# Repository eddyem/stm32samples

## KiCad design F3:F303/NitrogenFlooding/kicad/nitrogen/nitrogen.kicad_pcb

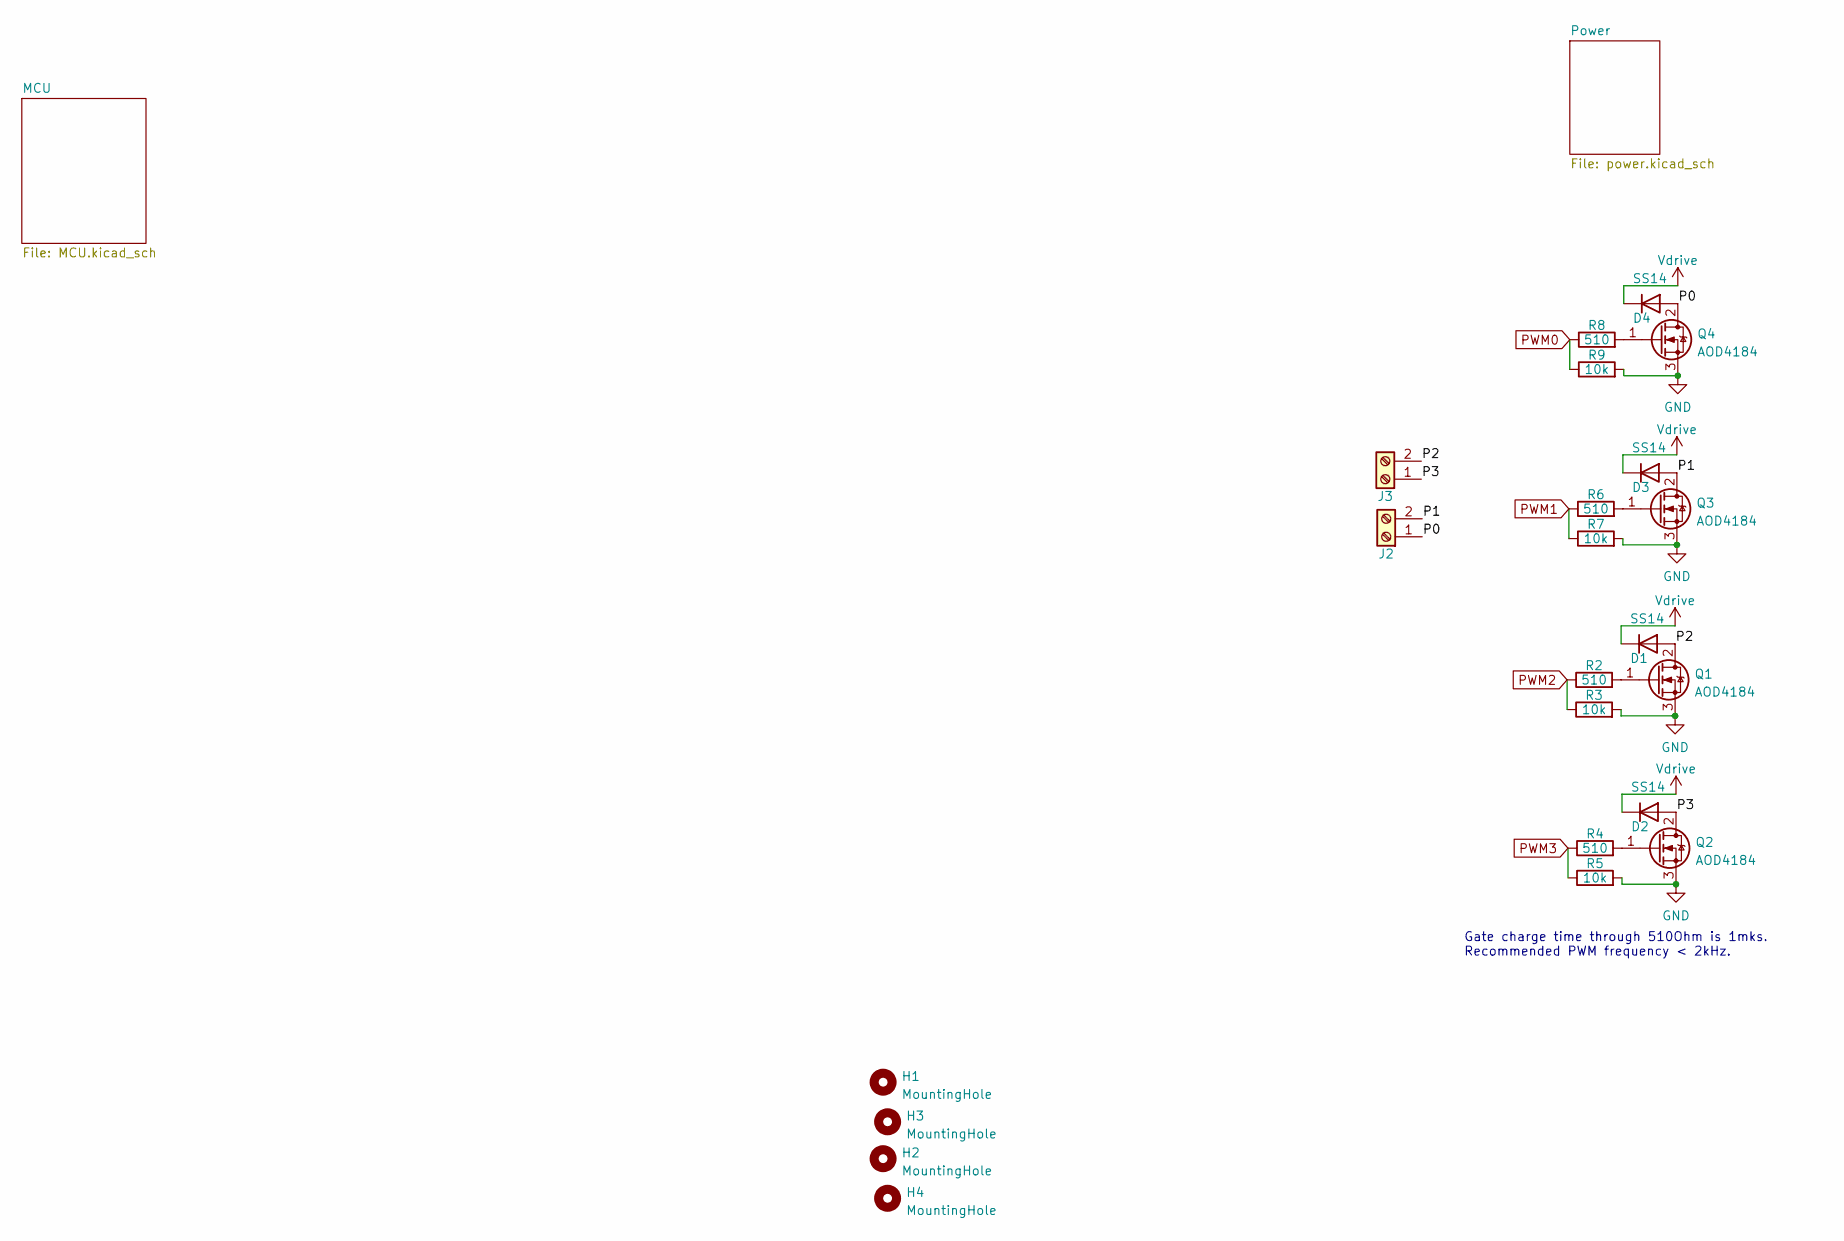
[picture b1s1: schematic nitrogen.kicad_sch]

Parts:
D1, D2, D3, D4: SS14; D_SMA_Handsoldering
H1, H2, H3, H4: MountingHole; MountingHole_3.2mm_M3_DIN965_Pad
J2, J3: Screw_Terminal_01x02; TerminalBlock_Phoenix_MKDS-1,5-2_1x02_P5.00mm_Horizontal
Q1, Q2, Q3, Q4: AOD4184; TO-252-2
R2, R4, R6, R8: 510; R_0603_1608Metric_Pad0.98x0.95mm_HandSolder
R3, R5, R7, R9: 10k; R_0603_1608Metric_Pad0.98x0.95mm_HandSolder

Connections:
/P0: D4.2 (A), J2.1, Q4.2 (D)
/P1: D3.2 (A), J2.2, Q3.2 (D)
/P2: D1.2 (A), J3.2, Q1.2 (D)
/P3: D2.2 (A), J3.1, Q2.2 (D)
GND: Q1.3 (S), Q2.3 (S), Q3.3 (S), Q4.3 (S), R3.2, R5.2, R7.2, R9.2; also elsewhere on the board
unnamed: Q1.1 (G), R2.2
unnamed: Q2.1 (G), R4.2
unnamed: Q3.1 (G), R6.2
unnamed: Q4.1 (G), R8.2
PWM0: R8.1, R9.1; also elsewhere on the board
PWM1: R6.1, R7.1; also elsewhere on the board
PWM2: R2.1, R3.1; also elsewhere on the board
PWM3: R4.1, R5.1; also elsewhere on the board
Vdrive: D1.1 (K), D2.1 (K), D3.1 (K), D4.1 (K); also elsewhere on the board

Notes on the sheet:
Gate charge time through 510Ohm is 1mks. Recommended PWM frequency < 2kHz.

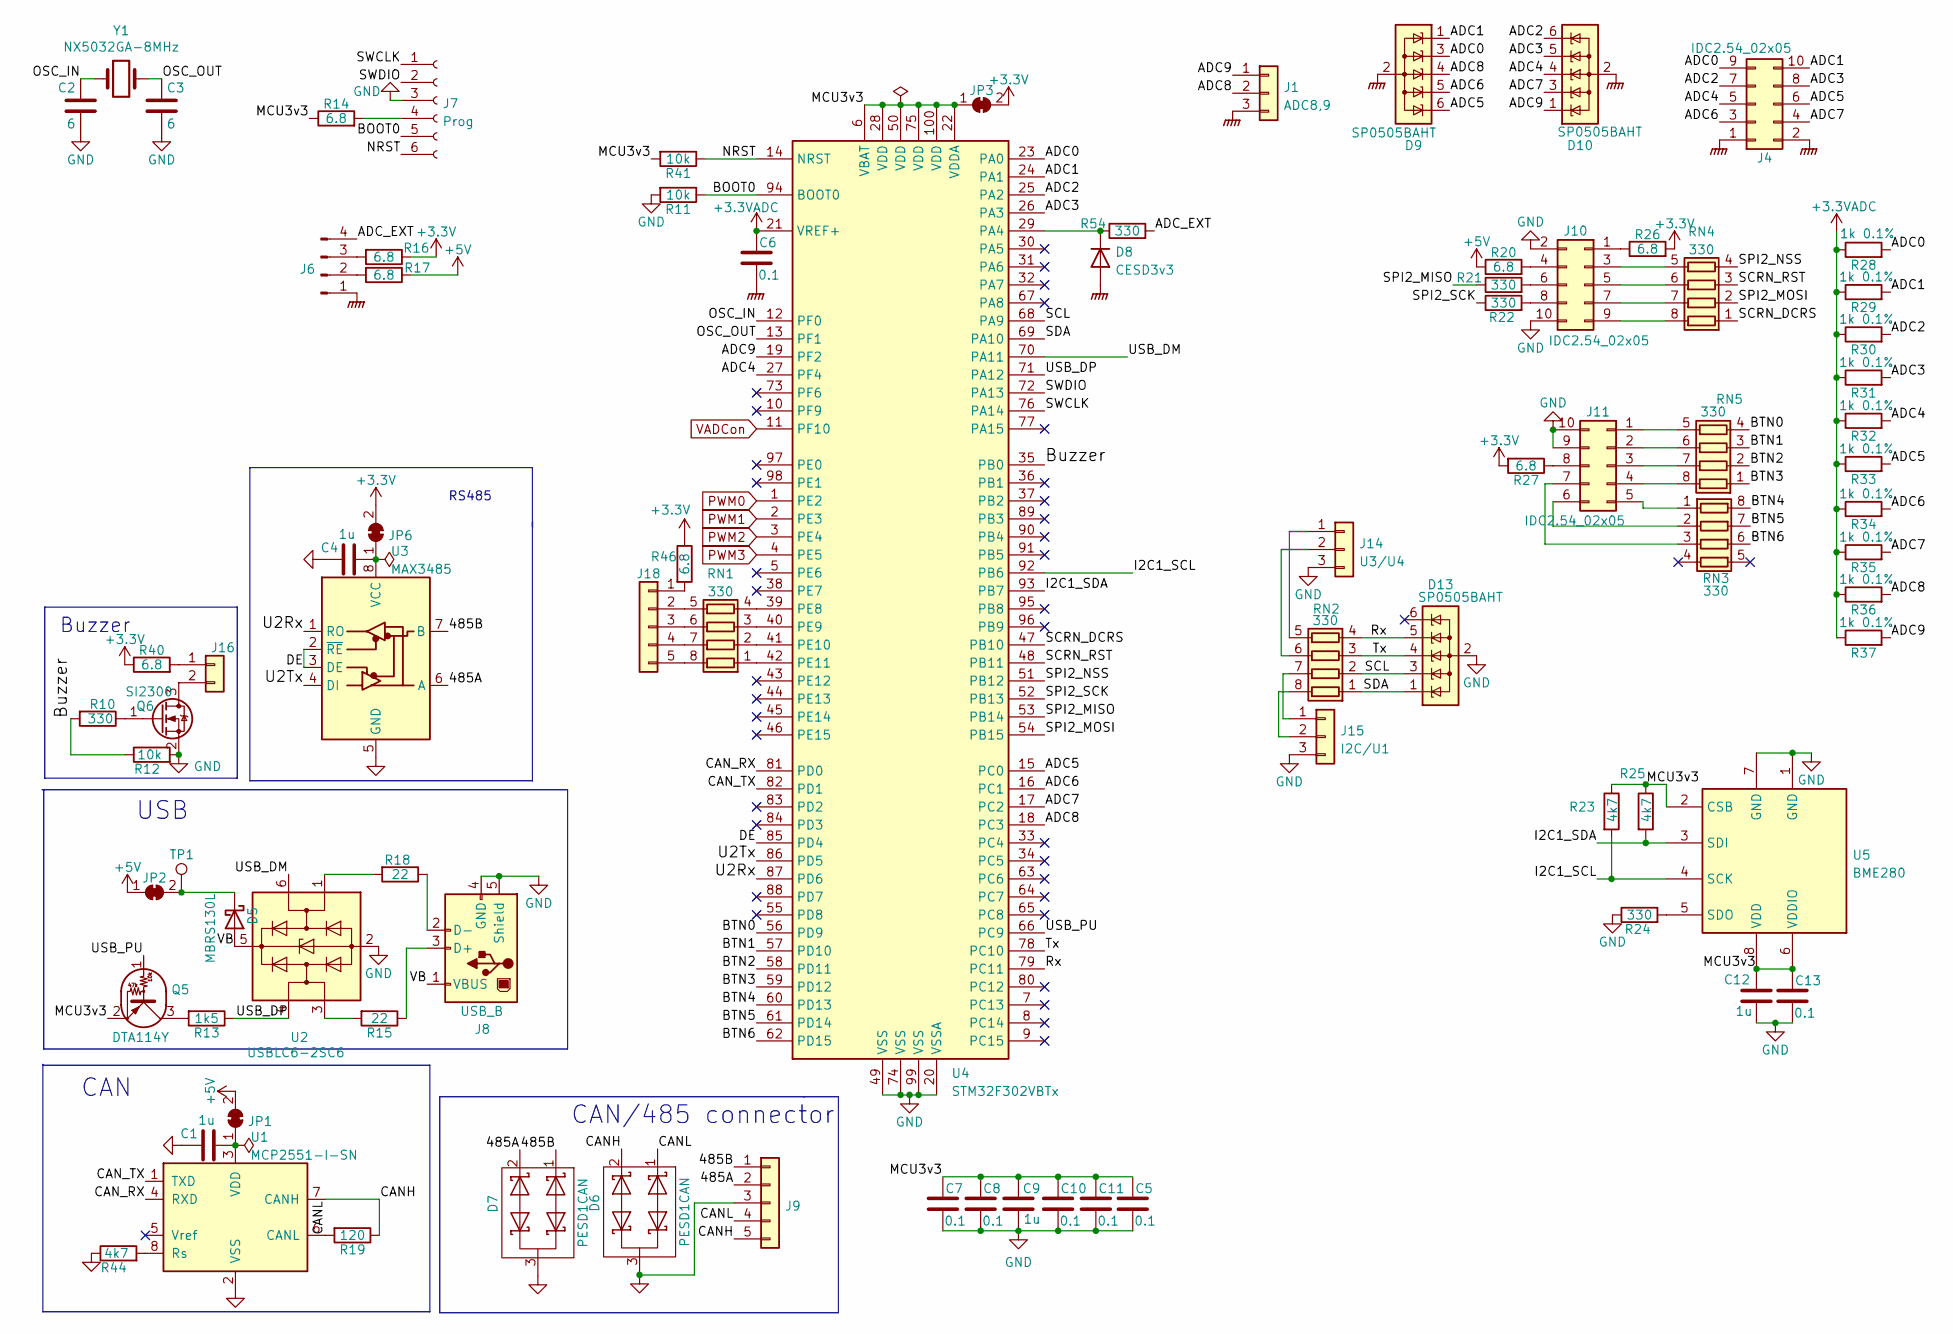
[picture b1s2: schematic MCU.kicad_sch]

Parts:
C1, C4, C9, C12: 1u; C_0603_1608Metric_Pad1.08x0.95mm_HandSolder
C2, C3: 6; C_0603_1608Metric_Pad1.08x0.95mm_HandSolder
C5, C6, C7, C8, C10, C11, C13: 0.1; C_0603_1608Metric_Pad1.08x0.95mm_HandSolder
D5: MBRS130L; D_SMB_Handsoldering
D6, D7: PESD1CAN; SOT-23
D8: CESD3v3; D_SOD-523
D9, D10, D13: SP0505BAHT; SOT-23-6
J1: ADC8,9; JST_EH_B3B-EH-A_1x03_P2.50mm_Vertical
J4, J10, J11: IDC2.54_02x05; IDC-Header_2x05_P2.54mm_Vertical
J6: ADCext; JST_EH_B4B-EH-A_1x04_P2.50mm_Vertical
J7: Prog; PinSocket_1x06_P1.27mm_Vertical
J8: USB_B; USB_B_TE_5787834_Vertical
J9: 485/CAN; JST_EH_B5B-EH-A_1x05_P2.50mm_Vertical
J14: U3/U4; JST_EH_B3B-EH-A_1x03_P2.50mm_Vertical
J15: I2C/U1; JST_EH_B3B-EH-A_1x03_P2.50mm_Vertical
J16: buzzer; PinSocket_1x02_P2.54mm_Vertical
J18: LEDs; JST_EH_B5B-EH-A_1x05_P2.50mm_Vertical
JP1: CAN; SolderJumper-2_P1.3mm_Open_TrianglePad1.0x1.5mm
JP2: USB5V; SolderJumper-2_P1.3mm_Open_TrianglePad1.0x1.5mm
JP3: MCU; SolderJumper-2_P1.3mm_Open_TrianglePad1.0x1.5mm
JP6: RS-485; SolderJumper-2_P1.3mm_Open_TrianglePad1.0x1.5mm
Q5: DTA114Y; SOT-323_SC-70_Handsoldering
Q6: SI2300; SOT-23_Handsoldering
R10, R21, R22, R24, R54: 330; R_0603_1608Metric_Pad0.98x0.95mm_HandSolder
R11, R12, R41: 10k; R_0603_1608Metric_Pad0.98x0.95mm_HandSolder
R13: 1k5; R_0603_1608Metric_Pad0.98x0.95mm_HandSolder
R14, R16, R17, R20, R26, R27, R40, R46: 6.8; R_0603_1608Metric_Pad0.98x0.95mm_HandSolder
R15, R18: 22; R_0603_1608Metric_Pad0.98x0.95mm_HandSolder
R19: 120; R_1210_3225Metric_Pad1.30x2.65mm_HandSolder
R23, R25, R44: 4k7; R_0603_1608Metric_Pad0.98x0.95mm_HandSolder
R28, R29, R30, R31, R32, R33, R34, R35, R36, R37: 1k 0.1%; R_0805_2012Metric_Pad1.20x1.40mm_HandSolder
RN1, RN2, RN3, RN4, RN5: 330; R_Array_Convex_4x0603
TP1: 5Vusb; TestPoint_THTPad_1.5x1.5mm_Drill0.7mm
U1: MCP2551-I-SN; SOIC-8_3.9x4.9mm_P1.27mm
U2: USBLC6-2SC6; SOT-23-6
U3: MAX3485; SO-8_3.9x4.9mm_P1.27mm
U4: STM32F302VBTx; LQFP-100_14x14mm_P0.5mm
U5: BME280; Bosch_LGA-8_2.5x2.5mm_P0.65mm_ClockwisePinNumbering
Y1: NX5032GA-8MHz; Crystal_SMD_5032-2Pin_5.0x3.2mm

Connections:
+3.3V: JP3.2 (B), JP6.2 (B), R16.1, R26.2, R27.2, R40.1, R46.1; also elsewhere on the board
+3.3VADC: C6.1, R28.1, R29.1, R30.1, R31.1, R32.1, R33.1, R34.1, R35.1, R36.1, R37.1, U4.21 (VREF+); also elsewhere on the board
+5V: JP1.2 (B), JP2.1 (A), R17.1, R20.1; also elsewhere on the board
/MCU/485A: D7.2 (K), J9.2, U3.6 (A)
/MCU/485B: D7.1 (K), J9.1, U3.7 (B)
/MCU/ADC0: D9.3 (K), J4.9, R28.2, U4.23 (PA0)
/MCU/ADC1: D9.1 (K), J4.10, R29.2, U4.24 (PA1)
/MCU/ADC2: D10.6 (K), J4.7, R30.2, U4.25 (PA2)
/MCU/ADC3: D10.5 (K), J4.8, R31.2, U4.26 (PA3)
/MCU/ADC4: D10.4 (K), J4.5, R32.2, U4.27 (PF4)
/MCU/ADC5: D9.6 (K), J4.6, R33.2, U4.15 (PC0)
/MCU/ADC6: D9.5 (K), J4.3, R34.2, U4.16 (PC1)
/MCU/ADC7: D10.3 (K), J4.4, R35.2, U4.17 (PC2)
/MCU/ADC8: D9.4 (K), J1.2, R36.2, U4.18 (PC3)
/MCU/ADC9: D10.1 (K), J1.1, R37.2, U4.19 (PF2)
/MCU/ADC_EXT: J6.4, R54.2
/MCU/BOOT0: J7.5, R11.1, U4.94 (BOOT0)
/MCU/BTN0: RN5.4 (R4.1), U4.56 (PD9)
/MCU/BTN1: RN5.3 (R3.1), U4.57 (PD10)
/MCU/BTN2: RN5.2 (R2.1), U4.58 (PD11)
/MCU/BTN3: RN5.1 (R1.1), U4.59 (PD12)
/MCU/BTN4: RN3.8 (R1.2), U4.60 (PD13)
/MCU/BTN5: RN3.7 (R2.2), U4.61 (PD14)
/MCU/BTN6: RN3.6 (R3.2), U4.62 (PD15)
/MCU/Buzzer: R10.2, R12.1, U4.35 (PB0)
/MCU/CANH: D6.2 (K), J9.5, R19.1, U1.7 (CANH)
/MCU/CANL: D6.1 (K), J9.4, R19.2, U1.6 (CANL)
/MCU/CAN_RX: U1.4 (RXD), U4.81 (PD0)
/MCU/CAN_TX: U1.1 (TXD), U4.82 (PD1)
/MCU/DE: U3.2 (~RE), U3.3 (DE), U4.85 (PD4)
/MCU/I2C1_SCL: R23.2, U4.92 (PB6), U5.4 (SCK)
/MCU/I2C1_SDA: R25.2, U4.93 (PB7), U5.3 (SDI)
/MCU/MCU3v3: C5.1, C7.1, C8.1, C9.1, C10.1, C11.1, C12.1, C13.1, JP3.1 (A), Q5.2 (E), R14.1, R23.1, R25.1, R41.2, U4.6 (VBAT), U4.22 (VDDA), U4.28 (VDD), U4.50 (VDD), U4.75 (VDD), U4.100 (VDD), U5.2 (CSB), U5.6 (VDDIO), U5.8 (VDD)
/MCU/NRST: J7.6, R41.1, U4.14 (NRST)
/MCU/OSC_IN: C2.1, U4.12 (PF0), Y1.1
/MCU/OSC_OUT: C3.1, U4.13 (PF1), Y1.2
/MCU/Rx: D13.5 (K), RN2.4 (R4.1), U4.79 (PC11)
/MCU/SCL: D13.3 (K), RN2.2 (R2.1), U4.68 (PA9)
/MCU/SCRN_DCRS: RN4.1 (R1.1), U4.47 (PB10)
/MCU/SCRN_RST: RN4.3 (R3.1), U4.48 (PB11)
/MCU/SDA: D13.1 (K), RN2.1 (R1.1), U4.69 (PA10)
/MCU/SPI2_MISO: R21.1, U4.53 (PB14)
/MCU/SPI2_MOSI: RN4.2 (R2.1), U4.54 (PB15)
/MCU/SPI2_NSS: RN4.4 (R4.1), U4.51 (PB12)
/MCU/SPI2_SCK: R22.1, U4.52 (PB13)
/MCU/SWCLK: J7.1, U4.76 (PA14)
/MCU/SWDIO: J7.2, U4.72 (PA13)
/MCU/Tx: D13.4 (K), RN2.3 (R3.1), U4.78 (PC10)
/MCU/U2Rx: U3.1 (RO), U4.87 (PD6)
/MCU/U2Tx: U3.4 (DI), U4.86 (PD5)
/MCU/USB_DM: U2.6 (I/O1), U4.70 (PA11)
/MCU/USB_DP: R13.1, U2.4 (I/O2), U4.71 (PA12)
/MCU/USB_PU: Q5.1 (B), U4.66 (PC9)
/MCU/VB: D5.2 (A), J8.1 (VBUS), U2.5 (VBUS)
GND: C1.1, C2.2, C3.2, C4.1, C5.2, C7.2, C8.2, C9.2, C10.2, C11.2, C12.2, C13.2, D6.3 (O), D7.3 (O), D13.2 (A), J7.3, J8.4 (GND), J8.5 (Shield), J9.3, J10.2, J10.10, J11.9, J11.10, J14.3, J15.3, Q6.2 (S), R11.2, R12.2, R24.1, R44.1, U1.2 (VSS), U2.2 (GND), U3.5 (GND), U4.20 (VSSA), U4.49 (VSS), U4.74 (VSS), U4.99 (VSS), U5.1 (GND), U5.7 (GND); also elsewhere on the board
GNDPWR: C6.2, D8.2 (A), D9.2 (A), D10.2 (A), J1.3, J4.1, J4.2, J6.1; also elsewhere on the board
unnamed: C1.2, JP1.1 (A), U1.3 (VDD)
unnamed: C4.2, JP6.1 (A), U3.8 (VCC)
unnamed: D5.1 (K), JP2.2 (B), TP1.1
unnamed: D8.1 (K), R54.1, U4.29 (PA4)
unnamed: J6.2, R17.2
unnamed: J6.3, R16.2
unnamed: J7.4, R14.2
unnamed: J8.2 (D-), R18.1
unnamed: J8.3 (D+), R15.1
unnamed: J10.1, R26.1
unnamed: J10.3, RN4.5 (R4.2)
unnamed: J10.4, R20.2
unnamed: J10.5, RN4.6 (R3.2)
unnamed: J10.6, R21.2
unnamed: J10.7, RN4.7 (R2.2)
unnamed: J10.8, R22.2
unnamed: J10.9, RN4.8 (R1.2)
unnamed: J11.1, RN5.5 (R4.2)
unnamed: J11.2, RN5.6 (R3.2)
unnamed: J11.3, RN5.7 (R2.2)
unnamed: J11.4, RN5.8 (R1.2)
unnamed: J11.5, RN3.1 (R1.1)
unnamed: J11.6, RN3.2 (R2.1)
unnamed: J11.7, RN3.3 (R3.1)
unnamed: J11.8, R27.1
unnamed: J14.1, RN2.5 (R4.2)
unnamed: J14.2, RN2.6 (R3.2)
unnamed: J15.1, RN2.7 (R2.2)
unnamed: J15.2, RN2.8 (R1.2)
unnamed: J16.1, R40.2
unnamed: J16.2, Q6.3 (D)
unnamed: J18.1, R46.2
unnamed: J18.2, RN1.5 (R4.2)
unnamed: J18.3, RN1.6 (R3.2)
unnamed: J18.4, RN1.7 (R2.2)
unnamed: J18.5, RN1.8 (R1.2)
unnamed: Q5.3 (C), R13.2
unnamed: Q6.1 (G), R10.1
unnamed: R15.2, U2.3 (I/O2)
unnamed: R18.2, U2.1 (I/O1)
unnamed: R24.2, U5.5 (SDO)
unnamed: R44.2, U1.8 (Rs)
unnamed: RN1.1 (R1.1), U4.42 (PE11)
unnamed: RN1.2 (R2.1), U4.41 (PE10)
unnamed: RN1.3 (R3.1), U4.40 (PE9)
unnamed: RN1.4 (R4.1), U4.39 (PE8)
PWM0: U4.1 (PE2); also elsewhere on the board
PWM1: U4.2 (PE3); also elsewhere on the board
PWM2: U4.3 (PE4); also elsewhere on the board
PWM3: U4.4 (PE5); also elsewhere on the board
VADCon: U4.11 (PF10); also elsewhere on the board

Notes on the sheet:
USB
RS485
Buzzer
CAN/485 connector
CAN

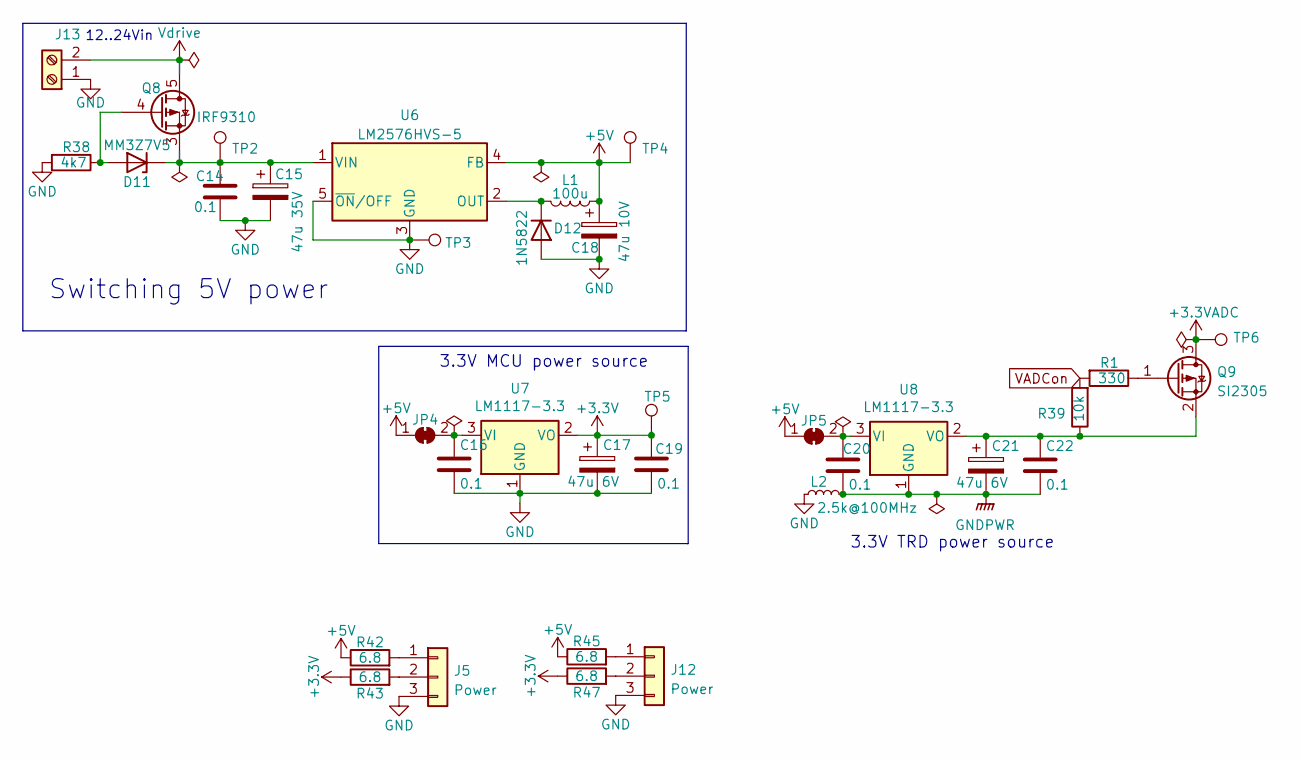
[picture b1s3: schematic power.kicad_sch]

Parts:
C14, C16, C19, C20, C22: 0.1; C_0603_1608Metric_Pad1.08x0.95mm_HandSolder
C15: 47u 35V; CP_EIA-6032-28_Kemet-C_Pad2.25x2.35mm_HandSolder
C17, C21: 47u 6V; CP_EIA-3216-18_Kemet-A_Pad1.58x1.35mm_HandSolder
C18: 47u 10V; CP_EIA-6032-28_Kemet-C_Pad2.25x2.35mm_HandSolder
D11: MM3Z7V5; D_0805_2012Metric_Pad1.15x1.40mm_HandSolder
D12: 1N5822; D_DO-201_P3.81mm_Vertical_AnodeUp
J5, J12: Power; JST_EH_B3B-EH-A_1x03_P2.50mm_Vertical
J13: Screw_Terminal_01x02; TerminalBlock_Phoenix_MKDS-1,5-2_1x02_P5.00mm_Horizontal
JP4: 3v3; SolderJumper-2_P1.3mm_Open_TrianglePad1.0x1.5mm
JP5: Vadc; SolderJumper-2_P1.3mm_Open_TrianglePad1.0x1.5mm
L1: 100u; L_Toroid_Horizontal_D6.5mm_P10.00mm_Diameter7-5mm_Amidon-T25
L2: 2.5k@100MHz; L_0805_2012Metric_Pad1.15x1.40mm_HandSolder
Q8: IRF9310; SO-8_3.9x4.9mm_P1.27mm
Q9: SI2305; SOT-23_Handsoldering
R1: 330; R_0603_1608Metric_Pad0.98x0.95mm_HandSolder
R38: 4k7; R_0603_1608Metric_Pad0.98x0.95mm_HandSolder
R39: 10k; R_0603_1608Metric_Pad0.98x0.95mm_HandSolder
R42, R43, R45, R47: 6.8; R_0603_1608Metric_Pad0.98x0.95mm_HandSolder
TP2: Vin; TestPoint_THTPad_1.5x1.5mm_Drill0.7mm
TP3: Gnd; TestPoint_THTPad_1.5x1.5mm_Drill0.7mm
TP4: 5V; TestPoint_THTPad_1.5x1.5mm_Drill0.7mm
TP5: 3.3V; TestPoint_THTPad_1.5x1.5mm_Drill0.7mm
TP6: Vadc; TestPoint_THTPad_1.5x1.5mm_Drill0.7mm
U6: LM2576HVS-5; TO-263-5_TabPin3
U7, U8: LM1117-3.3; SOT-223-3_TabPin2

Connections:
+3.3V: C17.1, C19.1, R43.1, R47.1, TP5.1, U7.2 (VO); also elsewhere on the board
+3.3VADC: Q9.3 (D), TP6.1; also elsewhere on the board
+5V: C18.1, JP4.1 (A), JP5.1 (A), L1.1, R42.1, R45.1, TP4.1, U6.4 (FB); also elsewhere on the board
GND: C14.2, C15.2, C16.2, C17.2, C18.2, C19.2, D12.2 (A), J5.3, J12.3, J13.1, L2.1, R38.2, TP3.1, U6.3 (GND), U6.5 (~ON/OFF), U7.1 (GND); also elsewhere on the board
GNDPWR: C20.2, C21.2, C22.2, L2.2, U8.1 (GND); also elsewhere on the board
unnamed: C14.1, C15.1, D11.1 (K), Q8.1 (S), Q8.2 (S), Q8.3 (S), TP2.1, U6.1 (VIN)
unnamed: C16.1, JP4.2 (B), U7.3 (VI)
unnamed: C20.1, JP5.2 (B), U8.3 (VI)
unnamed: C21.1, C22.1, Q9.2 (S), R39.1, U8.2 (VO)
unnamed: D11.2 (A), Q8.4 (G), R38.1
unnamed: D12.1 (K), L1.2, U6.2 (OUT)
unnamed: J5.1, R42.2
unnamed: J5.2, R43.2
unnamed: J12.1, R45.2
unnamed: J12.2, R47.2
unnamed: Q9.1 (G), R1.1
VADCon: R1.2, R39.2; also elsewhere on the board
Vdrive: J13.2, Q8.5 (D), Q8.6 (D), Q8.7 (D), Q8.8 (D); also elsewhere on the board

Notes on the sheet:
Switching 5V power
3.3V MCU power source
12..24Vin
3.3V TRD power source

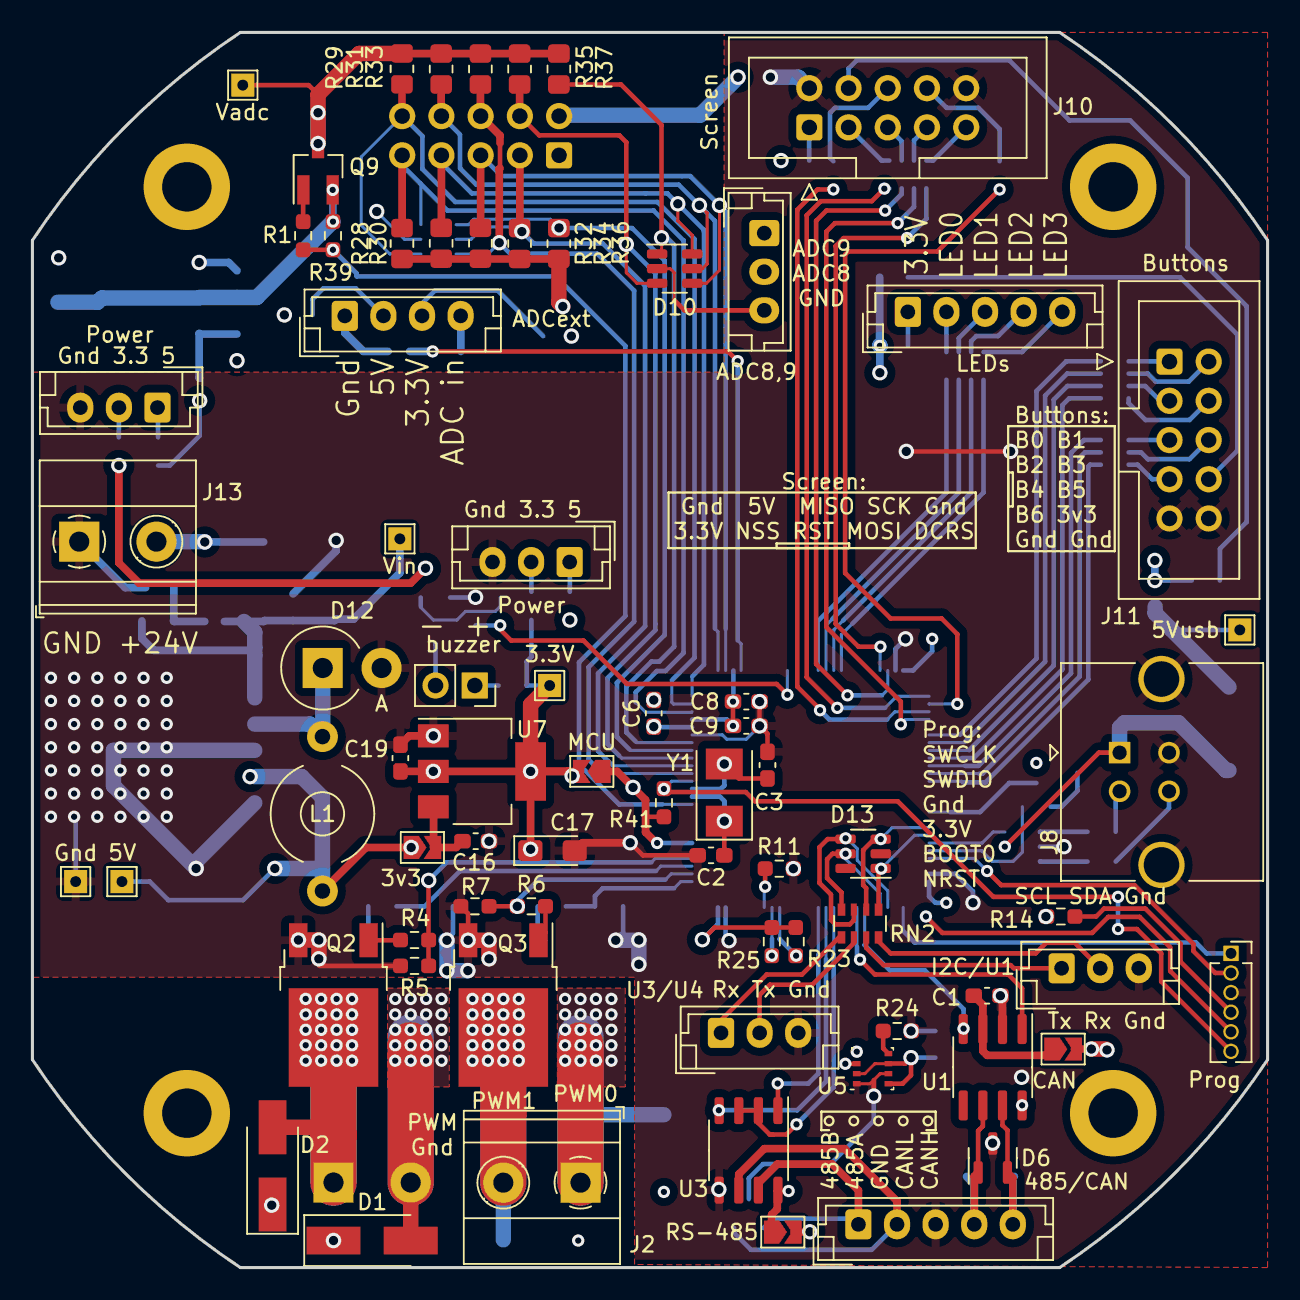
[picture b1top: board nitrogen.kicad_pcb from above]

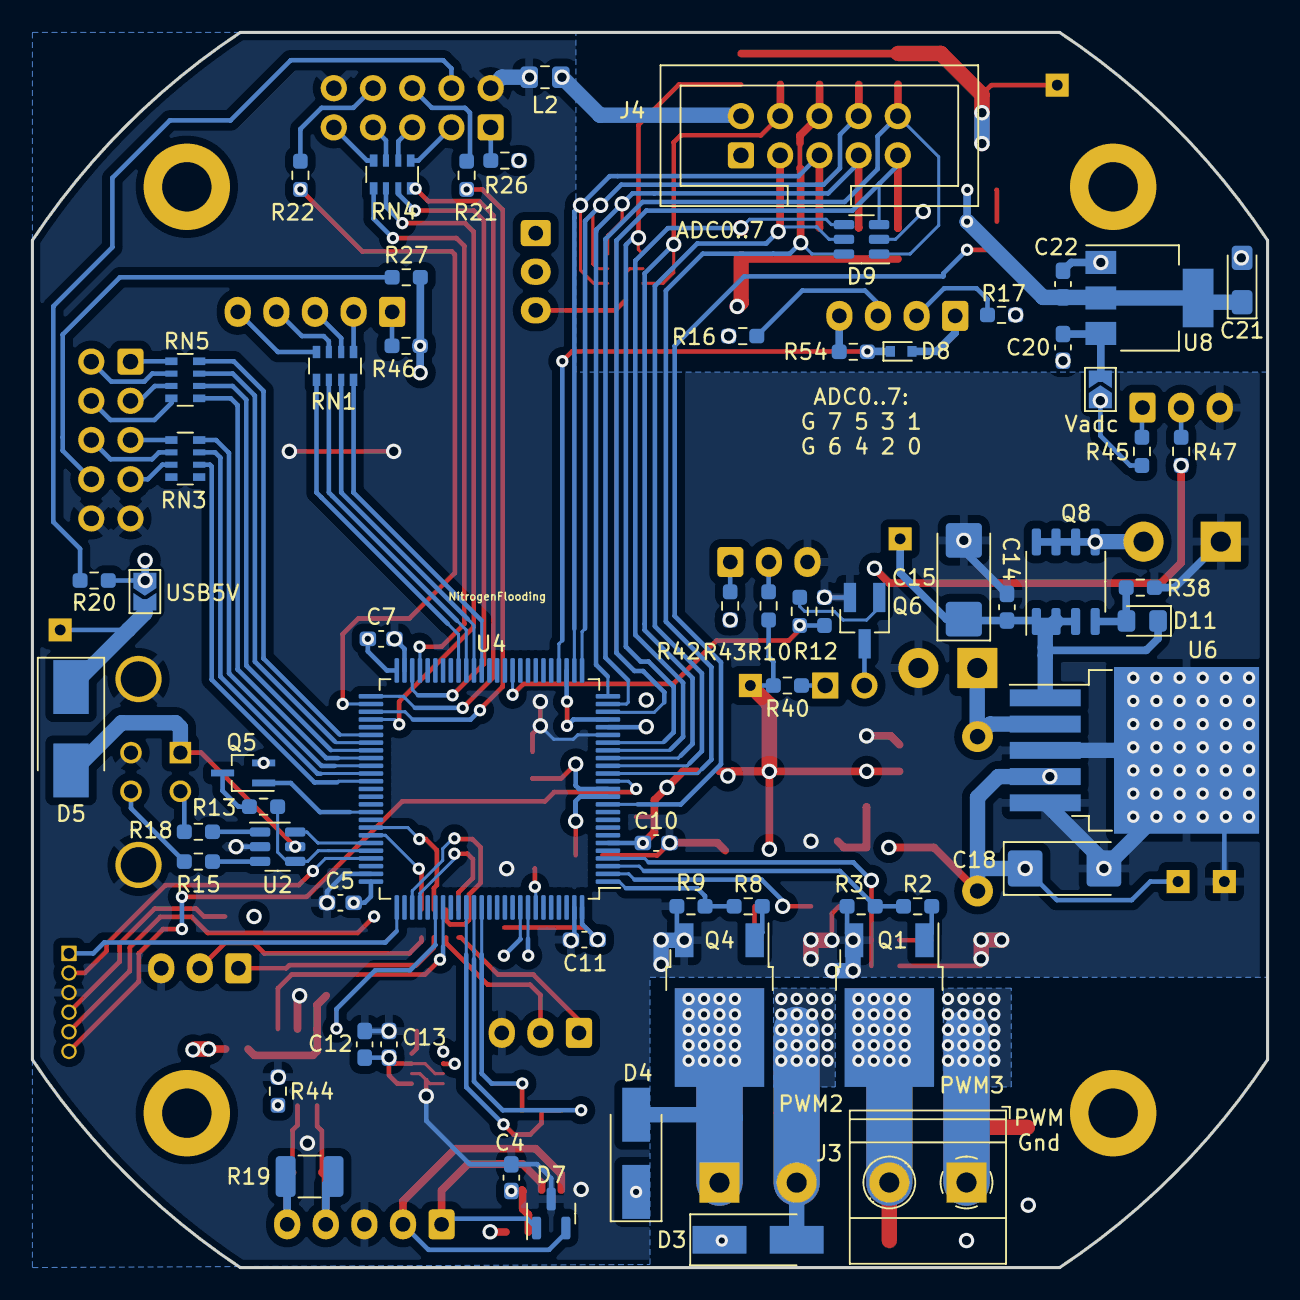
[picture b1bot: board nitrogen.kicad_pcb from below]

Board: 4 copper layers, 80.0 x 80.0 mm, 140 parts (64 on the bottom side), 127 nets.

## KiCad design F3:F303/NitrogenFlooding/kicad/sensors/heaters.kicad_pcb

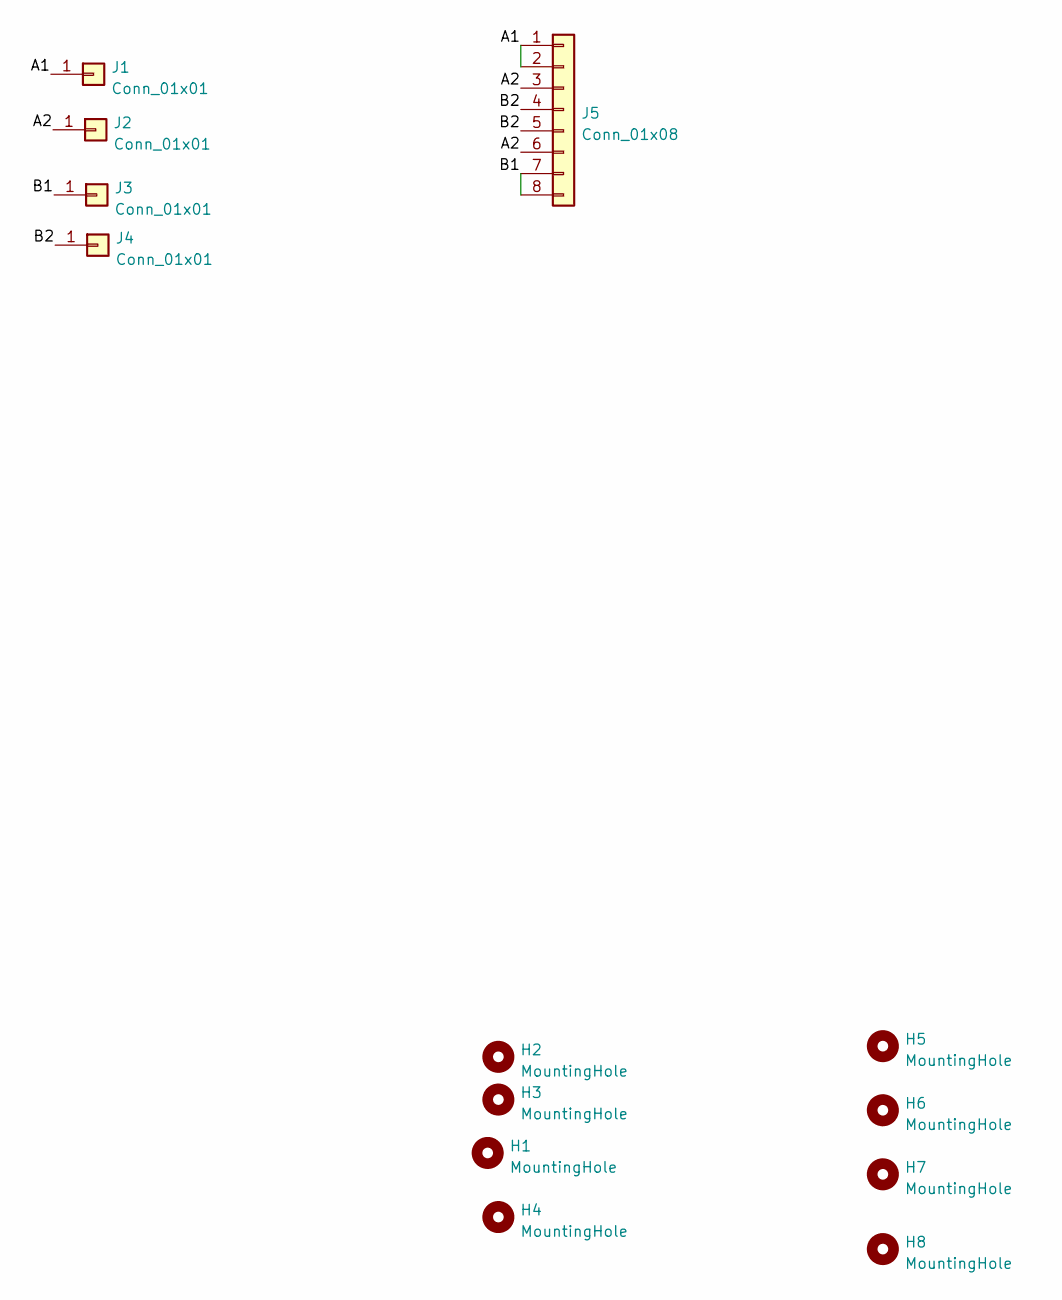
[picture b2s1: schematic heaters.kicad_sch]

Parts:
H1, H2, H3, H4: MountingHole; MountingHole_2mm
H5, H6, H7, H8: MountingHole; MountingHole_3.2mm_M3
J1, J2, J3, J4: Conn_01x01; PinSocket_1x01_P2.54mm_Vertical
J5: Conn_01x08; avia8

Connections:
/A1: J1.1, J5.1, J5.2
/A2: J2.1, J5.3, J5.6
/B1: J3.1, J5.7, J5.8
/B2: J4.1, J5.4, J5.5

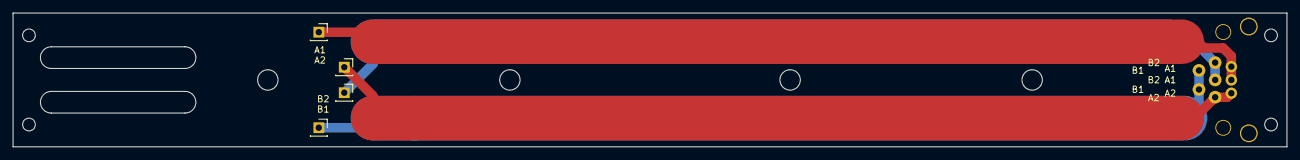
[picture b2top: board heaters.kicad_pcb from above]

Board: 2 copper layers, 200.0 x 21.0 mm, 13 parts (0 on the bottom side), 4 nets.

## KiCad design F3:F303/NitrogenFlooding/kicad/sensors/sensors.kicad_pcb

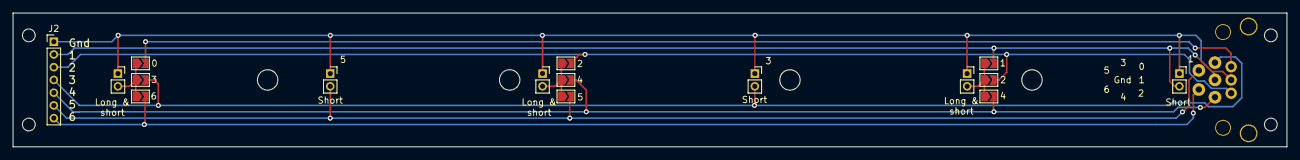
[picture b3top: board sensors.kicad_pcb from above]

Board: 2 copper layers, 200.0 x 21.0 mm, 25 parts (0 on the bottom side), 11 nets.

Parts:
H1, H2, H3, H4: MountingHole; MountingHole_2mm
H5, H6, H7, H8: MountingHole; MountingHole_3.2mm_M3
J1: Conn_01x08; avia8
J2: Conn_01x08; PinHeader_1x07_P2.00mm_Vertical
JP1: 1; SolderJumper-2_P1.3mm_Open_TrianglePad1.0x1.5mm
JP2, JP4: 2; SolderJumper-2_P1.3mm_Open_TrianglePad1.0x1.5mm
JP3, JP5: 4; SolderJumper-2_P1.3mm_Open_TrianglePad1.0x1.5mm
JP6: 5; SolderJumper-2_P1.3mm_Open_TrianglePad1.0x1.5mm
JP7: 0; SolderJumper-2_P1.3mm_Open_TrianglePad1.0x1.5mm
JP8: 3; SolderJumper-2_P1.3mm_Open_TrianglePad1.0x1.5mm
JP9: 6; SolderJumper-2_P1.3mm_Open_TrianglePad1.0x1.5mm
TH1, TH2, TH3, TH4, TH5, TH6: PT1000; PinSocket_1x02_P2.00mm_Vertical

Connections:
/S1: JP1.1 (A), JP2.1 (A), JP3.1 (A), TH2.2
/S3: JP4.1 (A), JP5.1 (A), JP6.1 (A), TH4.2
/S5: JP7.1 (A), JP8.1 (A), JP9.1 (A), TH6.2
/Sa0: J1.1, JP7.2 (B)
/Sa1: J1.2, J2.2, JP1.2 (B), TH1.2
/Sa2: J1.3, J2.3, JP2.2 (B), JP4.2 (B)
/Sa3: J1.4, J2.4, JP8.2 (B), TH3.2
/Sa4: J1.6, J2.5, JP3.2 (B), JP5.2 (B)
/Sa5: J1.7, J2.6, JP6.2 (B), TH5.2
/Sa6: J1.8, J2.7, JP9.2 (B)
GND: J1.5, J2.1, TH1.1, TH2.1, TH3.1, TH4.1, TH5.1, TH6.1

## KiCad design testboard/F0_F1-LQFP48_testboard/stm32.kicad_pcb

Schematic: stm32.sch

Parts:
C1, C2, C3, C7, C8, C9, C10: 0.1; C_0603_1608Metric_Pad1.05x0.95mm_HandSolder
C4: 47u; CP_EIA-3216-18_Kemet-A_Pad1.58x1.35mm_HandSolder
C5, C6: 12; C_0603_1608Metric_Pad1.05x0.95mm_HandSolder
D1: LED; LED_D3.0mm
D2: IP4220CZ6; SOT-23-6_Handsoldering
D3, D4: LED; LED_D5.0mm
P1: USART1; PinHeader_1x03_P2.54mm_Vertical
P2: USB_B; USB_Micro-B_Wuerth_629105150521
Q1: DTA114Y; SOT-323_SC-70_Handsoldering
R1, R2: 10k; R_0603_1608Metric_Pad1.05x0.95mm_HandSolder
R3: 100k; R_0603_1608Metric_Pad1.05x0.95mm_HandSolder
R4, R5, R6: 220; R_0805_2012Metric_Pad1.15x1.40mm_HandSolder
R7, R8: 22; R_0603_1608Metric_Pad1.05x0.95mm_HandSolder
R9: 1k5; R_0603_1608Metric_Pad1.05x0.95mm_HandSolder
RV1: 10k; Potentiometer
SW1: Reset; SW_PUSH_6mm
SW2: Boot; SW_PUSH_6mm
SW3: Button0; SW_PUSH_6mm
SW4: Button1; SW_PUSH_6mm
U1: LM1117-3.3; SOT-223
U2: STM32F042C6Tx; DIP-48_W15.24mm_Socket_LongPads
U3: USBLC6-2SC6; SOT-23-6_Handsoldering
Y1: 8MHz; Crystal_HC49-U_Vertical

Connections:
+3V3: C2.2, C3.1, C4.1, C7.2, C8.2, C9.2, C10.2, D1.2 (A), D2.5, D3.2 (A), D4.2 (A), Q1.2, R2.2, RV1.1, SW2.2, U1.2 (VO), U1.4 (VO), U2.1 (VBAT), U2.9 (VDDA), U2.24 (VDD), U2.36 (VDDIO2), U2.48 (VDD)
+5V: P2.1 (VBUS), U1.3 (VI), U3.5
/BOOT0: C2.1, R1.1, SW2.1, U2.44 (PF11)
/Button0: D2.6, SW4.1, U2.37 (SYS_SWCLK/USART2_TX/PA14)
/Button1: D2.4, SW3.1, U2.38 (I2S1_WS/SPI1_NSS/TIM2_CH1/TIM2_ETR/USAR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)
/LED0: R5.2, U2.14 (ADC_IN4/I2S1_WS/SPI1_NSS/TIM14_CH1/TSC_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)
/LED1: R6.2, U2.10 (ADC_IN0/RTC_TAMP2/SYS_WKUP1/TIM2_CH1/TI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)
/NRST: C1.1, R2.1, SW1.1, U2.7 (NRST)
/OSC_IN: C5.1, U2.5 (PF0/CRS_SYNC/I2C1_SDA/RCC_OSC_IN), Y1.1
/OSC_OUT: C6.1, U2.6 (PF1/I2C1_SCL/RCC_OSC_OUT), Y1.2
/Rx: D2.1, P1.3, U2.31 (I2C1_SDA/TIM17_BKIN/TIM1_CH3/TSC_G4_IO2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)
/Tx: D2.3, P1.2, U2.30 (I2C1_SCL/TIM1_CH2/TSC_G4_IO1/USART1_TX/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)
/USB_PU: Q1.1, U2.34 (IR_OUT/SYS_SWDIO/USB_OE/PA13)
GND: C1.2, C3.2, C4.2, C5.2, C6.2, C7.1, C8.1, C9.1, C10.1, D2.2, P1.1, P2.4 (GND), P2.5 (shield), R1.2, R3.2, R4.1, RV1.3, SW1.2, SW3.2, SW4.2, U1.1 (GND/ADJ), U2.8 (VSSA), U2.23 (VSS), U2.35 (VSS), U2.47 (VSS), U3.2
unnamed: D1.1 (K), R4.2
unnamed: D3.1 (K), R5.1
unnamed: D4.1 (K), R6.1
unnamed: P2.2 (D-), U3.6
unnamed: P2.3 (D+), R9.2, U3.4
unnamed: Q1.3, R9.1
unnamed: R3.1, U2.20 (PB2/TSC_G3_IO4)
unnamed: R7.1, U3.1
unnamed: R7.2, U2.32 (CAN_RX/I2C1_SCL/TIM1_CH4/TSC_G4_IO3/USA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)
unnamed: R8.1, U3.3
unnamed: R8.2, U2.33 (CAN_TX/I2C1_SDA/TIM1_ETR/TSC_G4_IO4/USA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)
unnamed: RV1.2, U2.18 (PB0/ADC_IN8/TIM1_CH2N/TIM3_CH3/TSC_G3_I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)

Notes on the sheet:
3.3V MCU power source
Bootloader init
Crystal for STM32F103
